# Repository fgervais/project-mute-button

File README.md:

# Mute Button

Convenient and fast ways to mute yourself in calls.

## PCB

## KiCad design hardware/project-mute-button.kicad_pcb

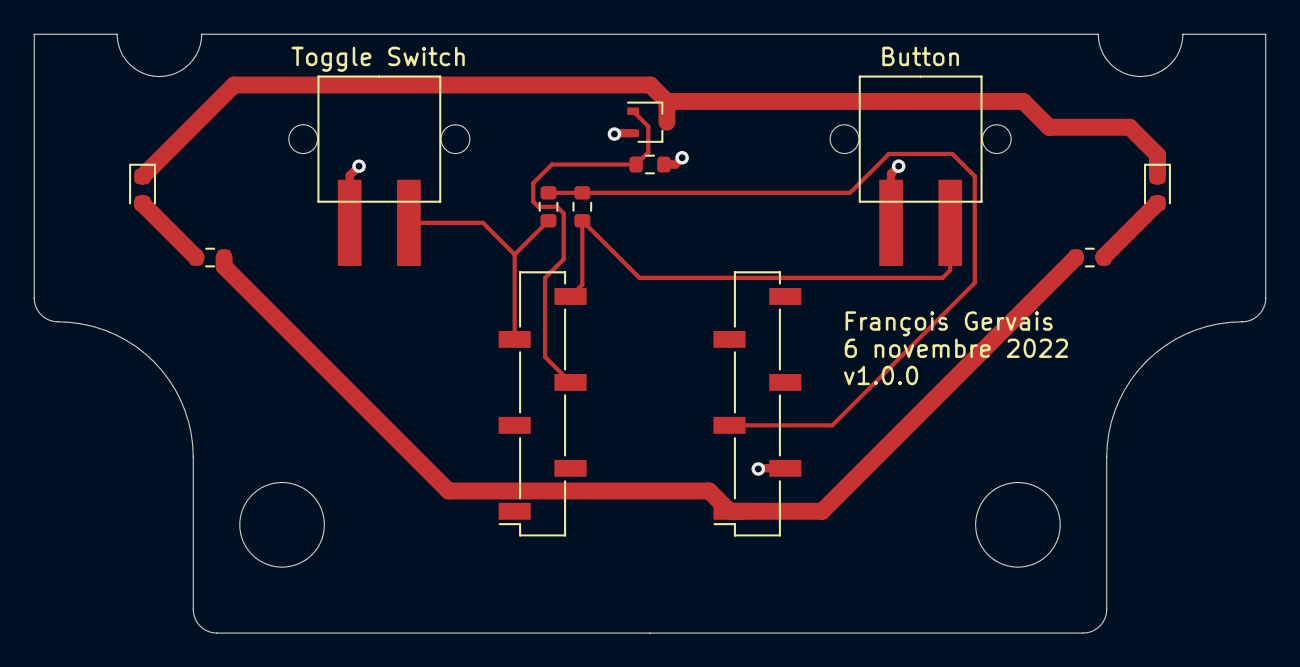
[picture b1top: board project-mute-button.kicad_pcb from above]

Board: 2 copper layers, 72.8 x 35.4 mm, 14 parts (0 on the bottom side), 9 nets.

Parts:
D1, D2: LED; LED_0603_1608Metric
H2, H4: MountingHole; MountingHole_5mm
J1, J2: Conn_01x06_Female; PinSocket_1x06_P2.54mm_Vertical_SMD_Pin1Right
J3: Button; TZ022101B000G
J4: Toggle Switch; TZ022101B000G
Q1: Q_NMOS_GSD; SOT-323_SC-70
R1, R2, R4: 10k; R_0603_1608Metric
R3, R5: 150; R_0603_1608Metric

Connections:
+3V3: J1.3, R1.1, R2.1
+5V: J1.1, R3.1, R5.1
/G0: J2.6, J3.1, R1.2
/G1: J2.5, J4.1, R2.2
/G2: J2.4, Q1.1, R4.1
GND: J1.2, J3.2, J4.2, Q1.2, R4.2
unnamed: D1.1, D2.1, Q1.3
unnamed: D1.2, R3.2
unnamed: D2.2, R5.2

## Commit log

2022-11-04 Blank structure with the library submodule
2022-11-04 First schematic draft
2022-11-04 Add 2 leds to schematic
2022-11-05 First placement with board shape
2022-11-05 Routing done
2022-11-06 Add version silk
2022-11-08 Refill ground pour
2022-11-08 Generate gerbers
2022-11-08 Remove the two mounting holes outside of board
2022-11-10 Change the middle half holes to 5mm
2022-11-10 Show user layer
2022-11-10 Regenerate gerbers
2022-11-13 Add first code draft
2022-11-13 Add case drawing
2022-12-08 Add assembly
2022-12-12 Run project in container
2022-12-13 Invert button and toggle switch
    To better fit how buttons are physically laid out.
2022-12-13 Update blinka
2022-12-14 Add images
2022-12-15 Allow mute/unmute
2022-12-16 Allow forcing unmute
2022-12-16 Fix inverted leds
